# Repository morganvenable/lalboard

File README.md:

##### lalboard - A 3D-printed keyboard inspired by the DataHand.

## Links

[More Images](https://github.com/JesusFreke/lalboard/wiki/Images)

[120 WPM Typing Demo](https://www.youtube.com/watch?v=oMhOIgrdeE0)

[V2 Project Logs (hackaday.io)](http://lalboard.com)

Online viewer for cluster assemblies:

- [finger](https://a360.co/3vxlLLL)
- [left thumb](https://a360.co/3c63TzE)
- [right thumb](https://a360.co/3c6tvws)

## Project Details

I am a long-time user of a DataHand keyboard. With the scarcity and rising cost of second hand
DataHands these days, I wanted to ensure that I always had access to a DataHand-like keyboard. And
so this project was born.

The overall functionality of the lalboard is obviously heavily based on the DataHand, but I designed
all of the specific key mechanisms, etc. from scratch, to be printable on a normal hobby-level
FDM printer.

With my DataHand, I never felt like I could get the keys positioned *quite right* for my hand. So
one of my primary focuses with the lalboard was adjustability. Each key cluster can be independently
adjusted in all 6 degrees of freedom to some extent.

Most parts need to be printed in a very opaque PLA, but there are a few parts that don't work well
in PLA which should be printed in polycarbonate or similar material, for its strength and heat
resistance.

##### Key Mechanisms

All keys use a pair of magnets to provide the clickiness and key return force, and an IR LED and
phototransistor for detecting a keypress. They are all held in place only with magnets, so they
are easily removable for cleaning, etc.

The feel/clickiness of the keys was another focus area. I tried to get them to feel as similar to
those on a DataHand as possible. They require roughly the same amount of force, and have that same
unique clicky feel due to the magnetic holding force.

##### Adjustability

The key clusters have a trio of standoffs that are designed to be mounted onto a steel sheet with
magnets. Each standoff has an adjustable height, and is mounted to the key cluster via a
ball socket. This provides a limited 6 degrees of freedom in adjusting the angle and position of
each key cluster, in order to get it perfectly positioned for your hands.

##### Fit

Fit is hard and individual.  Additionally, if you're not already a DH user, you'll be adjusting to the new mechanism, layout and typing style, too.  Doing all of this simultaneously can lead to overly fussy adjustment -- sometimes you just have to settle in.

Recommendations for fit:
Your hand should feel relaxed, and your palms should be supported beneath the center of the palm beneath the middle finger, at the minimum.  A palmrest that is too wide will cause discomfort in the outside of the hand, as the base of the pinky really wants to be able to curl around the palmrest a bit.

The palmrests should feel a little crazy tall compared to any other keyboard -- the motions are so small that you can get way more support from the palmrests on a lalboard/datahand.  That said, there are users who use the DH without palmrests at all, so it's a matter of experimentation and preference.  Start with rests, for sure because the relaxation of your hands from the high force, big motion world of traditional keyboards will take some time.

Finger position should be gently curved, maybe 45 degrees from vertical on the final knuckle to the keys -- too much curvature will cause a feeling of being cramped, with many unintentional N keypresses.  Too little will make you strain to hit the N keys.  You want to be able to relax and let your fingers extend naturally.

##### Electronics

As of V2, the lalboard uses standard PCBAs with a mix of SMT and through hole components.  The LEDs and phototransistors (PTs) are vertically mounted and side-firing, so they need to be soldered carefully to ensure they fit into the cluster body.  Once they are installed, there is little need for any additional fasteners, although a clamping screw hole is included in the design.

Each side of the keyboard uses an ESP32S2 MCU, and either can function as the USB connection to the PC.
The connections between the keys are 7 conductor JST cables which can be purchased directly on Amazon, and work fine.  If you want to make your own with nice silicone wires you can (see V1 readme), but the off-the-shelf ones do okay.

The halves are built flashed individually with separate Left and Right FW images that must each be built separately with a special command.
Noted here for convenience (assuming your device is on /dev/ttyACM0)
`SIDE=left idf.py -p /dev/ttyACM0 flash`
`SIDE=right idf.py -p /dev/ttyACM0 flash`
"SIDE" is an environment variable passed to the build system.

##### Handrest

The handrest was first molded for my wrist in plasticine clay, and then scanned in using the
[meshroom](https://github.com/alicevision/meshroom) photogrammetry software. Since they were molded
for my wrists specifically, I'm not sure how "one-size-fits-all" they are, or how comfortable they
would be for someone else to use.

##### [BOM](https://github.com/JesusFreke/lalboard/wiki/BOM)

##### [Printing tips & instructions](https://github.com/JesusFreke/lalboard/wiki/Printing-tips-&-instructions)

--------

Note: This is not an officially supported Google product.

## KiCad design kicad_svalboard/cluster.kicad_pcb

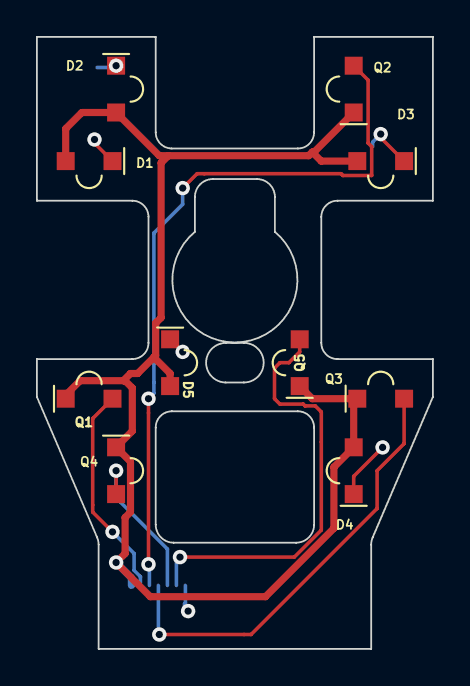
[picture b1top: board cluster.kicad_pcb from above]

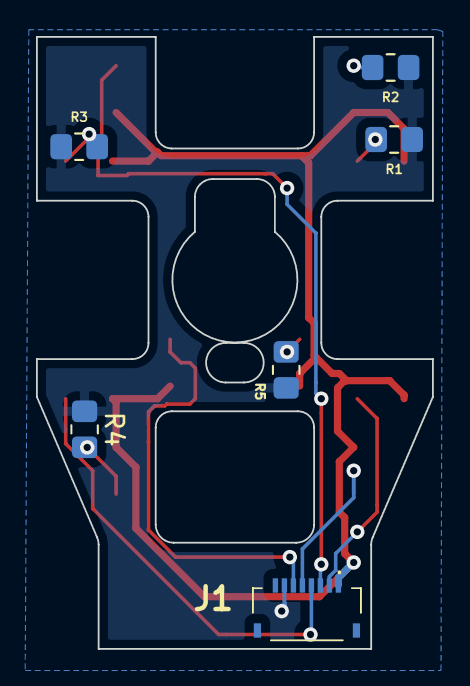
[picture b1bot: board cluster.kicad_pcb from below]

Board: 2 copper layers, 22.0 x 34.0 mm, 16 parts (6 on the bottom side), 12 nets.

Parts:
D1, D2, D3, D4, D5: IR12-21C
J1: Conn_01x07; FH34SRJ8S05SH50
Q1, Q2, Q3, Q4, Q5: PT12-21B
R1, R2, R3, R4, R5: 270; R_0805_2012Metric_Pad1.20x1.40mm_HandSolder

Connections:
+5V: D1.1 (K), D2.1 (K), D3.1 (K), D4.1 (K), D5.1 (K), J1.1, Q1.1 (C), Q2.1 (C), Q3.1 (C), Q4.1 (C), Q5.1 (C)
C1: J1.2, Q1.2 (E)
C2: J1.3, Q2.2 (E)
C3: J1.4, Q3.2 (E)
C4: J1.5, Q4.2 (E)
C5: J1.6, Q5.2 (E)
GND: J1.7, R1.1, R2.1, R3.1, R4.1, R5.1
unnamed: D1.2 (A), R1.2
unnamed: D2.2 (A), R2.2
unnamed: D3.2 (A), R3.2
unnamed: D4.2 (A), R4.2
unnamed: D5.2 (A), R5.2

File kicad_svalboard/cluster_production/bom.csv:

Designator,Footprint,Quantity,Value,LCSC Part #
J1,FH34SRJ8S05SH50,1,Conn_01x07,
Q2,PT12-21B,1,PT12-21B,C264383
Q5,PT12-21B,1,PT12-21B,C264383
D3,IR12-21C,1,IR12-21C,C53672
D1,IR12-21C,1,IR12-21C,C53672
Q4,PT12-21B,1,PT12-21B,C264383
D4,IR12-21C,1,IR12-21C,C53672
Q3,PT12-21B,1,PT12-21B,C264383
Q1,PT12-21B,1,PT12-21B,C264383
D5,IR12-21C,1,IR12-21C,C53672
D2,IR12-21C,1,IR12-21C,C53672
R5,R_0805_2012Metric_Pad1.20x1.40mm_HandSolder,1,270,
R2,R_0805_2012Metric_Pad1.20x1.40mm_HandSolder,1,270,
R1,R_0805_2012Metric_Pad1.20x1.40mm_HandSolder,1,270,
R4,R_0805_2012Metric_Pad1.20x1.40mm_HandSolder,1,270,
R3,R_0805_2012Metric_Pad1.20x1.40mm_HandSolder,1,270,

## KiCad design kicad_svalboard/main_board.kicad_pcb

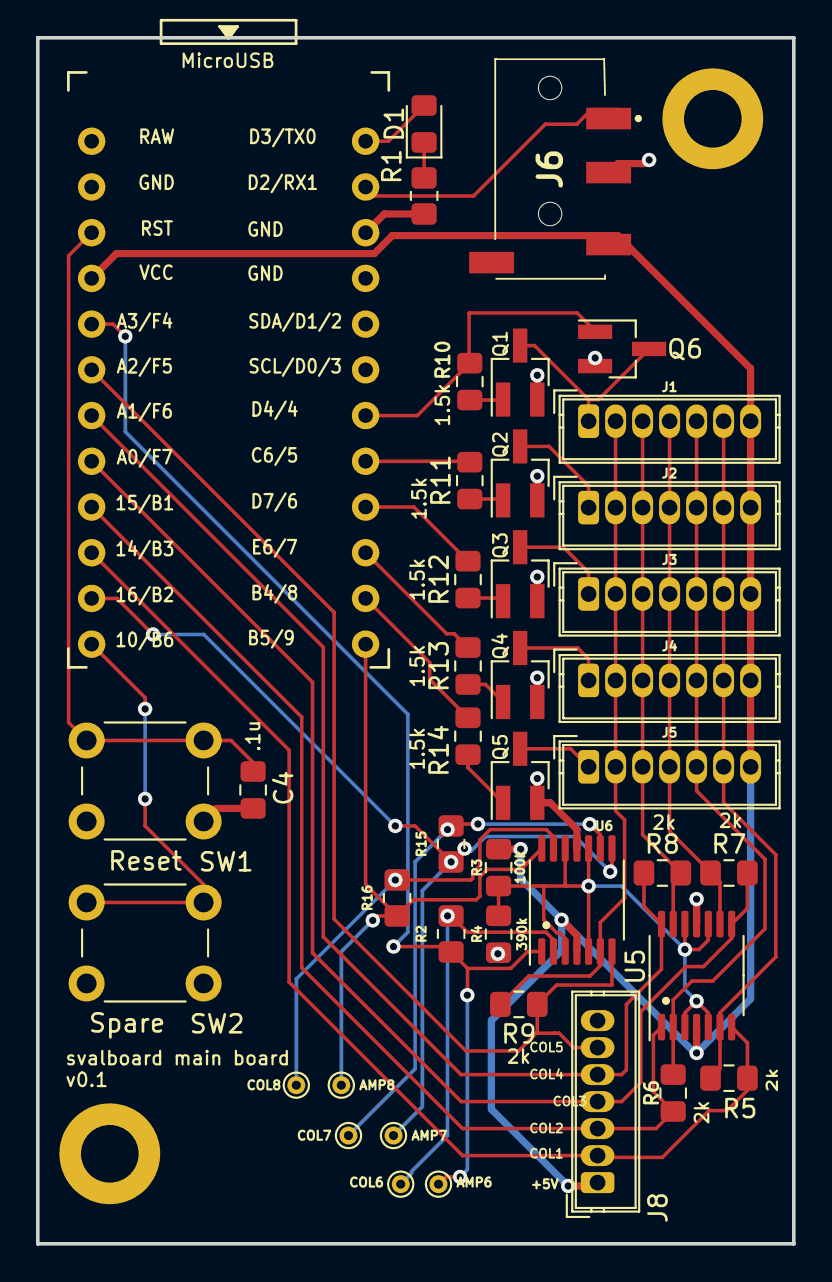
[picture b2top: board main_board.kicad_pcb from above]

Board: 2 copper layers, 42.0 x 67.0 mm, 44 parts (0 on the bottom side), 39 nets.

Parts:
AMP6, AMP7, AMP8: TestPoint; TestPoint_THTPad_D1.0mm_Drill0.5mm
C4: .1u; C_0805_2012Metric_Pad1.15x1.40mm_HandSolder
COL6, COL7, COL8: TestPoint; TestPoint_THTPad_D1.0mm_Drill0.5mm
D1: LED; LED_0805_2012Metric_Pad1.15x1.40mm_HandSolder
H1, H2: MountingHole_Pad; MountingHole_3.2mm_M3_DIN965_Pad
J1, J2, J3, J4, J5, J8: Conn_01x07; JST_ZH_B7B-ZR_1x07_P1.50mm_Vertical
J6: PJ-320D
Q1, Q2, Q3, Q4, Q5: Q_NPN_BEC; SOT-23_Handsoldering
Q6: Q_NMOS_GSD; SOT-23_Handsoldering
R1: 5k; R_0805_2012Metric_Pad1.20x1.40mm_HandSolder
R2, R15, R16: 2k; R_0805_2012Metric_Pad1.20x1.40mm_HandSolder
R3: 100k; R_0805_2012Metric_Pad1.15x1.40mm_HandSolder
R4: 390k; R_0805_2012Metric_Pad1.15x1.40mm_HandSolder
R5, R6, R7, R8, R9: 2k; R_0805_2012Metric_Pad1.15x1.40mm_HandSolder
R10, R11, R12, R13, R14: 1.5k; R_0805_2012Metric_Pad1.15x1.40mm_HandSolder
SW1: Reset; SW_PUSH_6mm_H5mm
SW2: Spare; SW_PUSH_6mm_H5mm
U1: ProMicro; ProMicro_v3.5
U5, U6: LMV324; TSSOP-14_4.4x5mm_P0.65mm

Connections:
+5V: J1.7, J2.7, J3.7, J4.7, J5.7, J6.4, J8.1, R3.1, U1.21 (VCC), U5.4 (V+), U6.4 (V+)
/AMP_REF: R3.2, R4.1, U5.3 (+), U5.5 (+), U5.10 (+), U5.12 (+), U6.3 (+), U6.5 (+), U6.10 (+), U6.12 (+)
/COL1: J1.6, J2.6, J3.6, J4.6, J5.6, R5.2, U5.6 (-)
/COL1_AMP: J8.2, R5.1, U1.15 (B3), U5.7
/COL2: J1.5, J2.5, J3.5, J4.5, J5.5, R6.2, U5.2 (-)
/COL2_AMP: J8.3, R6.1, U1.16 (B1), U5.1
/COL3: J1.4, J2.4, J3.4, J4.4, J5.4, R7.2, U5.9 (-)
/COL3_AMP: J8.4, R7.1, U1.17 (F7), U5.8
/COL4: J1.3, J2.3, J3.3, J4.3, J5.3, R8.2, U5.13 (-)
/COL4_AMP: J8.5, R8.1, U1.18 (F6), U5.14
/COL5: J1.2, J2.2, J3.2, J4.2, J5.2, R9.2, U6.6 (-)
/COL5_AMP: J8.6, R9.1, U1.19 (F5), U6.7
/COL6: COL6.1, R2.2, U6.2 (-)
/COL6_AMP: AMP6.1, R2.1, U1.20 (F4), U6.1
/COL7: COL7.1, R15.2, U6.9 (-)
/COL7_AMP: AMP7.1, R15.1, U1.14 (B2), U6.8
/COL8: COL8.1, R16.2, U6.13 (-)
/COL8_AMP: AMP8.1, R16.1, U1.12 (B5), U6.14
/DATA: J6.2, U1.2 (RX)
/LED: D1.2 (A), U1.1 (TX)
/RESET: C4.2, SW1.1, U1.22 (RST)
/ROW1: R14.2, U1.11 (B4)
/ROW2: R13.2, U1.10 (E6)
/ROW3: R12.2, U1.9 (D7)
/ROW4: R11.2, U1.8 (C6)
/ROW5: Q6.1 (G), R10.2, U1.7 (D4)
/SPARE: SW2.1, U1.13 (B6)
GND: C4.1, H1.1, H2.1, J6.3, J8.7, Q1.2 (E), Q2.2 (E), Q3.2 (E), Q4.2 (E), Q5.2 (E), Q6.2 (S), R1.2, R4.2, SW1.2, SW2.2, U1.3 (GND), U1.4 (GND), U1.23 (GND), U5.11 (V-), U6.11 (V-)
unnamed: D1.1 (K), R1.1
unnamed: J1.1, Q1.3 (C), Q6.3 (D)
unnamed: J2.1, Q2.3 (C)
unnamed: J3.1, Q3.3 (C)
unnamed: J4.1, Q4.3 (C)
unnamed: J5.1, Q5.3 (C)
unnamed: Q1.1 (B), R10.1
unnamed: Q2.1 (B), R11.1
unnamed: Q3.1 (B), R12.1
unnamed: Q4.1 (B), R13.1
unnamed: Q5.1 (B), R14.1

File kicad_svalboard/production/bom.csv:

Designator,Footprint,Quantity,Value,LCSC Part #
C4,C_0805_2012Metric_Pad1.15x1.40mm_HandSolder,1,.1u,C28233
J1,JST_ZH_B7B-ZR_1x07_P1.50mm_Vertical,1,Conn_01x07,C157978
J3,JST_ZH_B7B-ZR_1x07_P1.50mm_Vertical,1,Conn_01x07,C157978
J4,JST_ZH_B7B-ZR_1x07_P1.50mm_Vertical,1,Conn_01x07,C157978
J5,JST_ZH_B7B-ZR_1x07_P1.50mm_Vertical,1,Conn_01x07,C157978
J2,JST_ZH_B7B-ZR_1x07_P1.50mm_Vertical,1,Conn_01x07,C157978
J8,JST_ZH_B7B-ZR_1x07_P1.50mm_Vertical,1,Conn_01x07,C157978
D1,LED_0805_2012Metric_Pad1.15x1.40mm_HandSolder,1,LED,C2297
H1,MountingHole_3.2mm_M3_DIN965_Pad,1,MountingHole_Pad,
H2,MountingHole_3.2mm_M3_DIN965_Pad,1,MountingHole_Pad,
J6,PJ-320D,1,PJ-320D,C521460
U1,ProMicro_v3.5,1,ProMicro,C2874015
R11,R_0805_2012Metric_Pad1.15x1.40mm_HandSolder,1,1.5k,C4310
R12,R_0805_2012Metric_Pad1.15x1.40mm_HandSolder,1,1.5k,C4310
R13,R_0805_2012Metric_Pad1.15x1.40mm_HandSolder,1,1.5k,C4310
R10,R_0805_2012Metric_Pad1.15x1.40mm_HandSolder,1,1.5k,C4310
R14,R_0805_2012Metric_Pad1.15x1.40mm_HandSolder,1,1.5k,C4310
R3,R_0805_2012Metric_Pad1.15x1.40mm_HandSolder,1,100k,C149504
R5,R_0805_2012Metric_Pad1.15x1.40mm_HandSolder,1,2k,C17604
R8,R_0805_2012Metric_Pad1.15x1.40mm_HandSolder,1,2k,C17604
R7,R_0805_2012Metric_Pad1.15x1.40mm_HandSolder,1,2k,C17604
R9,R_0805_2012Metric_Pad1.15x1.40mm_HandSolder,1,2k,C17604
R6,R_0805_2012Metric_Pad1.15x1.40mm_HandSolder,1,2k,C17604
R4,R_0805_2012Metric_Pad1.15x1.40mm_HandSolder,1,390k,C17656
R1,R_0805_2012Metric_Pad1.20x1.40mm_HandSolder,1,5k,C352178
Q6,SOT-23_Handsoldering,1,Q_NMOS_GSD,C5122029
Q4,SOT-23_Handsoldering,1,Q_NPN_BEC,C23869
Q5,SOT-23_Handsoldering,1,Q_NPN_BEC,C23869
Q1,SOT-23_Handsoldering,1,Q_NPN_BEC,C23869
Q3,SOT-23_Handsoldering,1,Q_NPN_BEC,C23869
Q2,SOT-23_Handsoldering,1,Q_NPN_BEC,C23869
SW2,SW_PUSH_6mm_H5mm,1,Boot,C428628
SW1,SW_PUSH_6mm_H5mm,1,Reset,C428628
U5,TSSOP-14_4.4x5mm_P0.65mm,1,LMV324,C398929
U6,TSSOP-14_4.4x5mm_P0.65mm,1,LMV324,C398929

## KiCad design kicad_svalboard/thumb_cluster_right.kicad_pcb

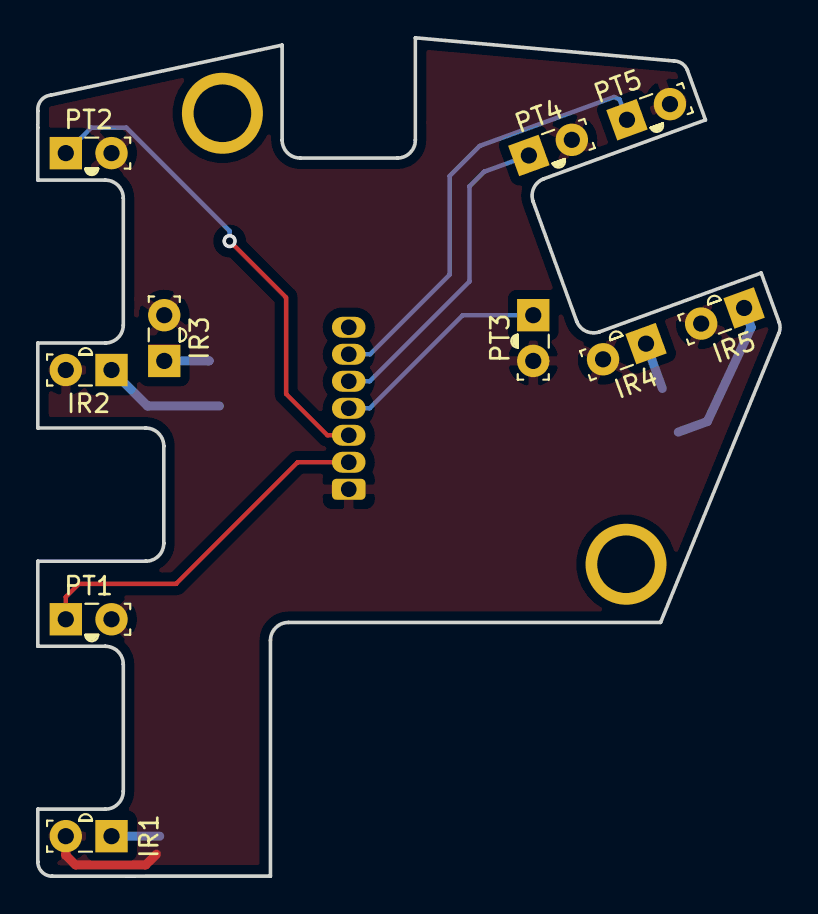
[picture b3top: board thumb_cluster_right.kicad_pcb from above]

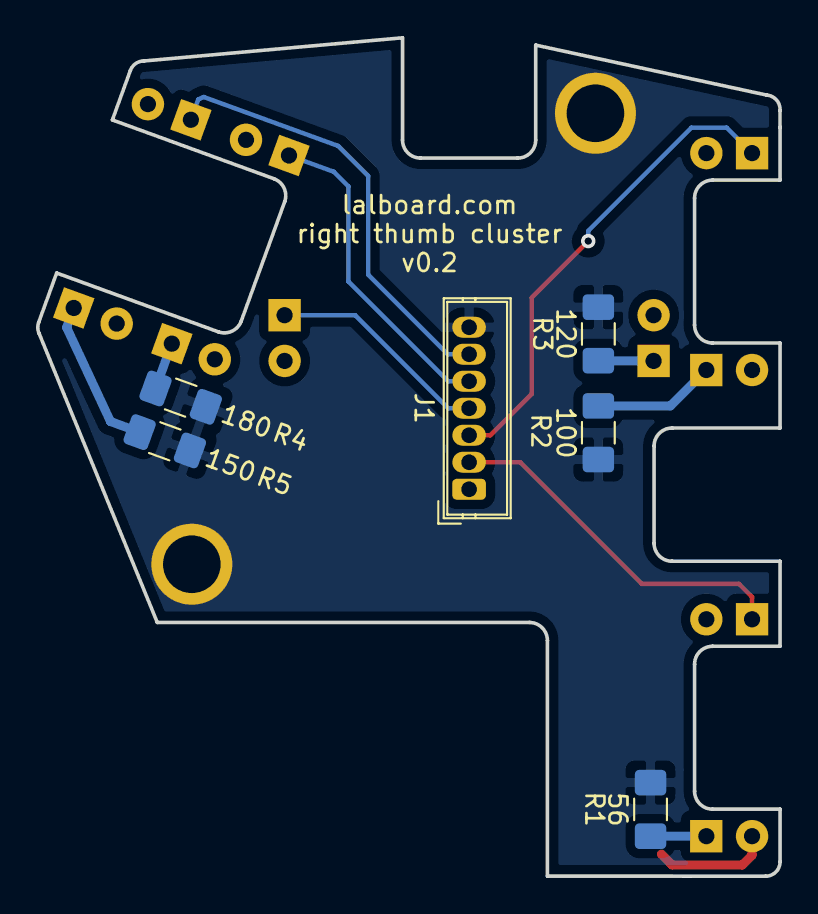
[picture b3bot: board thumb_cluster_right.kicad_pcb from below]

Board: 2 copper layers, 41.2 x 46.6 mm, 18 parts (6 on the bottom side), 12 nets.

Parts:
H1, H2: MountingHole_Pad; MountingHole_3.2mm_M3_Pad
IR1, IR2, IR3, IR4, IR5: IR908-7C-F
J1: Conn_01x07; JST_ZH_B7B-ZR_1x07_P1.50mm_Vertical
PT1, PT2, PT3, PT4, PT5: PT908-7B-F; PT908-7C-F
R1: 56; R_1206_3216Metric_Pad1.42x1.75mm_HandSolder
R2: 100; R_1206_3216Metric_Pad1.42x1.75mm_HandSolder
R3: 120; R_1206_3216Metric_Pad1.42x1.75mm_HandSolder
R4: 180; R_1206_3216Metric_Pad1.42x1.75mm_HandSolder
R5: 150; R_1206_3216Metric_Pad1.42x1.75mm_HandSolder

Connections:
+5V: IR1.2, IR2.2, IR3.2, IR4.2, IR5.2, J1.1, PT1.2, PT2.2, PT3.2, PT4.2, PT5.2
C1: J1.2, PT1.1
C2: J1.3, PT2.1
C3: J1.4, PT3.1
C4: J1.5, PT4.1
C5: J1.6, PT5.1
GND: H1.1, H2.1, J1.7, R1.1, R2.1, R3.1, R4.1, R5.1
unnamed: IR1.1, R1.2
unnamed: IR2.1, R2.2
unnamed: IR3.1, R3.2
unnamed: IR4.1, R4.2
unnamed: IR5.1, R5.2

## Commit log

2022-10-04 Bulk backup of Kicad branch.
2022-10-19 Removed datasheets folder, updated design with layouts for cluster and main PCB. still need FFC connectors on main PCB
2022-11-17 fixing a mess
2022-12-21 readme updates for v2
